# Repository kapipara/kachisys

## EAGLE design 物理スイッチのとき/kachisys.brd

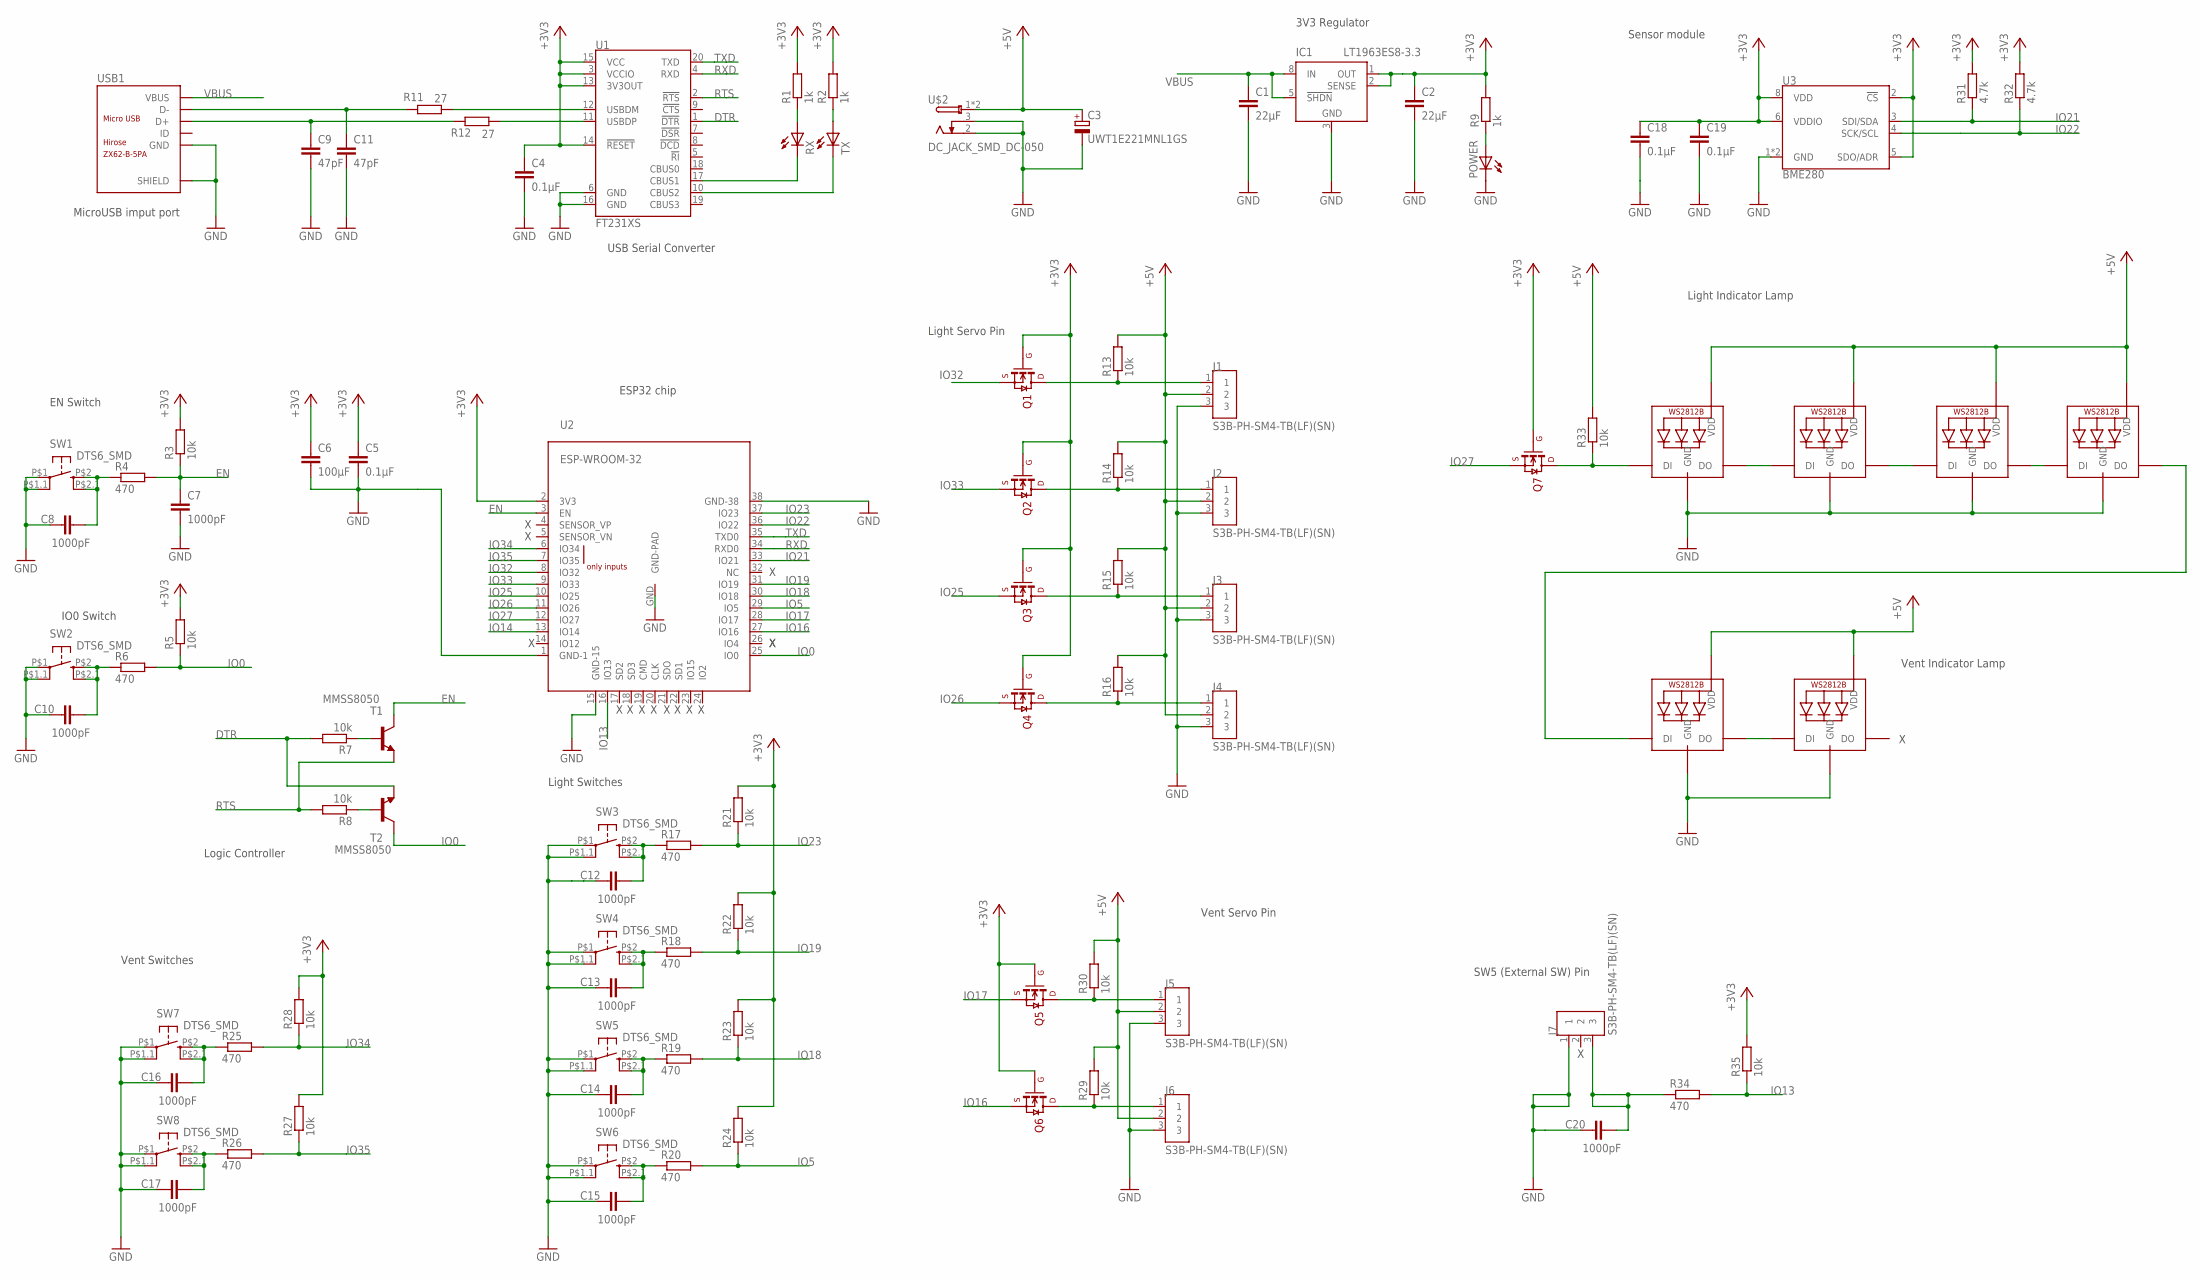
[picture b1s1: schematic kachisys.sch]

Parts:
C1, C2: 22μF; C2012
C3: UWT1E221MNL1GS; NICHICON-ALMINUM-CAPACITOR-8MM
C4, C5, C18, C19: 0.1μF; C0603
C6: 100μF; C3225
C7, C8, C10, C12, C13, C14, C15, C16, C17, C20: 1000pF; C0603
C9, C11: 47pF; C1608
IC1: LT1963ES8-3.3; SOIC8
J1, J2, J3, J4, J5, J6, J7: S3B-PH-SM4-TB(LF)(SN); JST_S3B-PH-SM4-TB(LF)(SN)
LED1, LED2, LED3, LED4, LED5, LED6: WS2812B_5050N; WS2812B-NARROW
POWER: LEDCHIP-LED0603; CHIP-LED0603
Q1, Q2, Q3, Q4, Q5, Q6, Q7: BSS138; SOT-23
R1, R2, R9: 1k; R0603
R3, R5, R7, R8, R13, R14, R15, R16, R21, R22, R23, R24, R27, R28, R29, R30, R33, R35: 10k; R0603
R4, R6, R17, R18, R19, R20, R25, R26, R34: 470; R0603
R11, R12: 27; R0603
R31, R32: 4.7k; R0603
RX: LEDCHIP-LED0603; CHIP-LED0603
SW1, SW2, SW3, SW4, SW5, SW6, SW7, SW8: DTS6_SMD; SKRPACE010
T1, T2: MMSS8050; SOT23-EBC
TX: LEDCHIP-LED0603; CHIP-LED0603
U1: FT231XS; SSOP20_L
U2: ESP-WROOM-32
U3: BME280; LGA-8-2.5X2.5
U$2: DC_JACK_SMD_DC-050
USB1: ZX62-B-5PA; MICRO-USB5+6P-SMD-0.65-AB

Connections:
+3V3: C2.1, C4.1, C5.1, C6.1, C18.1, C19.1, IC1.1 (OUT), IC1.2 (SENSE), Q1.G, Q2.G, Q3.G, Q4.G, Q5.G, Q6.G, Q7.G, R1.2, R2.2, R3.2, R5.2, R9.2, R21.2, R22.2, R23.2, R24.2, R27.2, R28.2, R31.2, R32.2, R35.2, U1.3 (VCCIO), U1.13 (3V3OUT), U1.14 (!RESET), U1.15 (VCC), U2.2 (3V3), U3.2 (!CS), U3.5 (SDO/ADR), U3.6 (VDDIO), U3.8 (VDD)
+5V: C3.POS (+), J1.2, J2.2, J3.2, J4.2, J5.2, J6.2, LED1.1-VDD (VDD), LED2.1-VDD (VDD), LED3.1-VDD (VDD), LED4.1-VDD (VDD), LED5.1-VDD (VDD), LED6.1-VDD (VDD), R13.2, R14.2, R15.2, R16.2, R29.2, R30.2, R33.2, U$2.1, U$2.1-1 (1)
DTR: R7.2, T2.E, U1.1 (!DTR)
EN: C7.1, R3.1, R4.2, T1.C, U2.3 (EN)
GND: C1.2, C2.2, C3.NEG (-), C4.2, C5.2, C6.2, C7.2, C8.1, C9.2, C10.1, C11.2, C12.1, C13.1, C14.1, C15.1, C16.1, C17.1, C18.2, C19.2, C20.1, IC1.3 (GND), IC1.6 (GND), IC1.7 (GND), J1.3, J2.3, J3.3, J4.3, J5.3, J6.3, J7.1, LED1.3-GND (GND), LED2.3-GND (GND), LED3.3-GND (GND), LED4.3-GND (GND), LED5.3-GND (GND), LED6.3-GND (GND), POWER.C, SW1.P$1, SW1.P$1.1 (P1), SW2.P$1, SW2.P$1.1 (P1), SW3.P$1, SW3.P$1.1 (P1), SW4.P$1, SW4.P$1.1 (P1), SW5.P$1, SW5.P$1.1 (P1), SW6.P$1, SW6.P$1.1 (P1), SW7.P$1, SW7.P$1.1 (P1), SW8.P$1, SW8.P$1.1 (P1), U1.6 (GND), U1.16 (GND), U2.1 (GND-1), U2.15 (GND-15), U2.38 (GND-38), U2.GND (GND-PAD), U3.1 (GND), U3.7 (GND), U$2.2, U$2.3, USB1.5 (GND), USB1.P1 (SHIELD), USB1.P2 (SHIELD), USB1.P3 (SHIELD), USB1.P4 (SHIELD), USB1.P5 (SHIELD), USB1.P6 (SHIELD)
IO0: R5.1, R6.2, T2.C, U2.25 (IO0)
IO5: R20.2, R24.1, U2.29 (IO5)
IO13: R34.2, R35.1, U2.16 (IO13)
IO14: U2.13 (IO14)
IO16: Q6.S, U2.27 (IO16)
IO17: Q5.S, U2.28 (IO17)
IO18: R19.2, R23.1, U2.30 (IO18)
IO19: R18.2, R22.1, U2.31 (IO19)
IO21: R31.1, U2.33 (IO21), U3.3 (SDI/SDA)
IO22: R32.1, U2.36 (IO22), U3.4 (SCK/SCL)
IO23: R17.2, R21.1, U2.37 (IO23)
IO25: Q3.S, U2.10 (IO25)
IO26: Q4.S, U2.11 (IO26)
IO27: Q7.S, U2.12 (IO27)
IO32: Q1.S, U2.8 (IO32)
IO33: Q2.S, U2.9 (IO33)
IO34: R25.2, R28.1, U2.6 (IO34)
IO35: R26.2, R27.1, U2.7 (IO35)
unnamed: C11.1, R11.2, USB1.2 (D-)
unnamed: C9.1, R12.2, USB1.3 (D+)
unnamed: RX.C, U1.17 (CBUS1)
unnamed: TX.C, U1.10 (CBUS2)
unnamed: C8.2, R4.1, SW1.P$2 (S), SW1.P$2.1 (S1)
unnamed: R1.1, RX.A
unnamed: R2.1, TX.A
unnamed: R7.1, T1.B
unnamed: R8.1, T2.B
unnamed: POWER.A, R9.1
unnamed: C10.2, R6.1, SW2.P$2 (S), SW2.P$2.1 (S1)
unnamed: R11.1, U1.12 (USBDM)
unnamed: R12.1, U1.11 (USBDP)
unnamed: J1.1, Q1.D, R13.1
unnamed: J2.1, Q2.D, R14.1
unnamed: J3.1, Q3.D, R15.1
unnamed: J4.1, Q4.D, R16.1
unnamed: C12.2, R17.1, SW3.P$2 (S), SW3.P$2.1 (S1)
unnamed: LED1.2-DOUT (DO), LED2.4-DIN (DI)
unnamed: C13.2, R18.1, SW4.P$2 (S), SW4.P$2.1 (S1)
unnamed: C14.2, R19.1, SW5.P$2 (S), SW5.P$2.1 (S1)
unnamed: C15.2, R20.1, SW6.P$2 (S), SW6.P$2.1 (S1)
unnamed: LED2.2-DOUT (DO), LED3.4-DIN (DI)
unnamed: C16.2, R25.1, SW7.P$2 (S), SW7.P$2.1 (S1)
unnamed: C17.2, R26.1, SW8.P$2 (S), SW8.P$2.1 (S1)
unnamed: LED3.2-DOUT (DO), LED4.4-DIN (DI)
unnamed: LED4.2-DOUT (DO), LED5.4-DIN (DI)
unnamed: J5.1, Q5.D, R30.1
unnamed: J6.1, Q6.D, R29.1
unnamed: LED5.2-DOUT (DO), LED6.4-DIN (DI)
unnamed: LED1.4-DIN (DI), Q7.D, R33.1
unnamed: C20.2, J7.3, R34.1
RTS: R8.2, T1.E, U1.2 (!RTS)
RXD: U1.4 (RXD), U2.34 (RXD0)
TXD: U1.20 (TXD), U2.35 (TXD0)
VBUS: C1.1, IC1.5 (!SHDN), IC1.8 (IN), USB1.1 (VBUS)

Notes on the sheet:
3V3 Regulator
USB Serial Converter
MicroUSB imput port
EN Switch
IO0 Switch
Logic Controller
ESP32 chip
Light Servo Pin
Light Switches
Vent Switches
Sensor module
Vent Servo Pin
Light Indicator Lamp
Vent Indicator Lamp
SW5 (External SW) Pin

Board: 2 copper layers, 93 parts (0 on the bottom side), 58 nets, no tracks yet.

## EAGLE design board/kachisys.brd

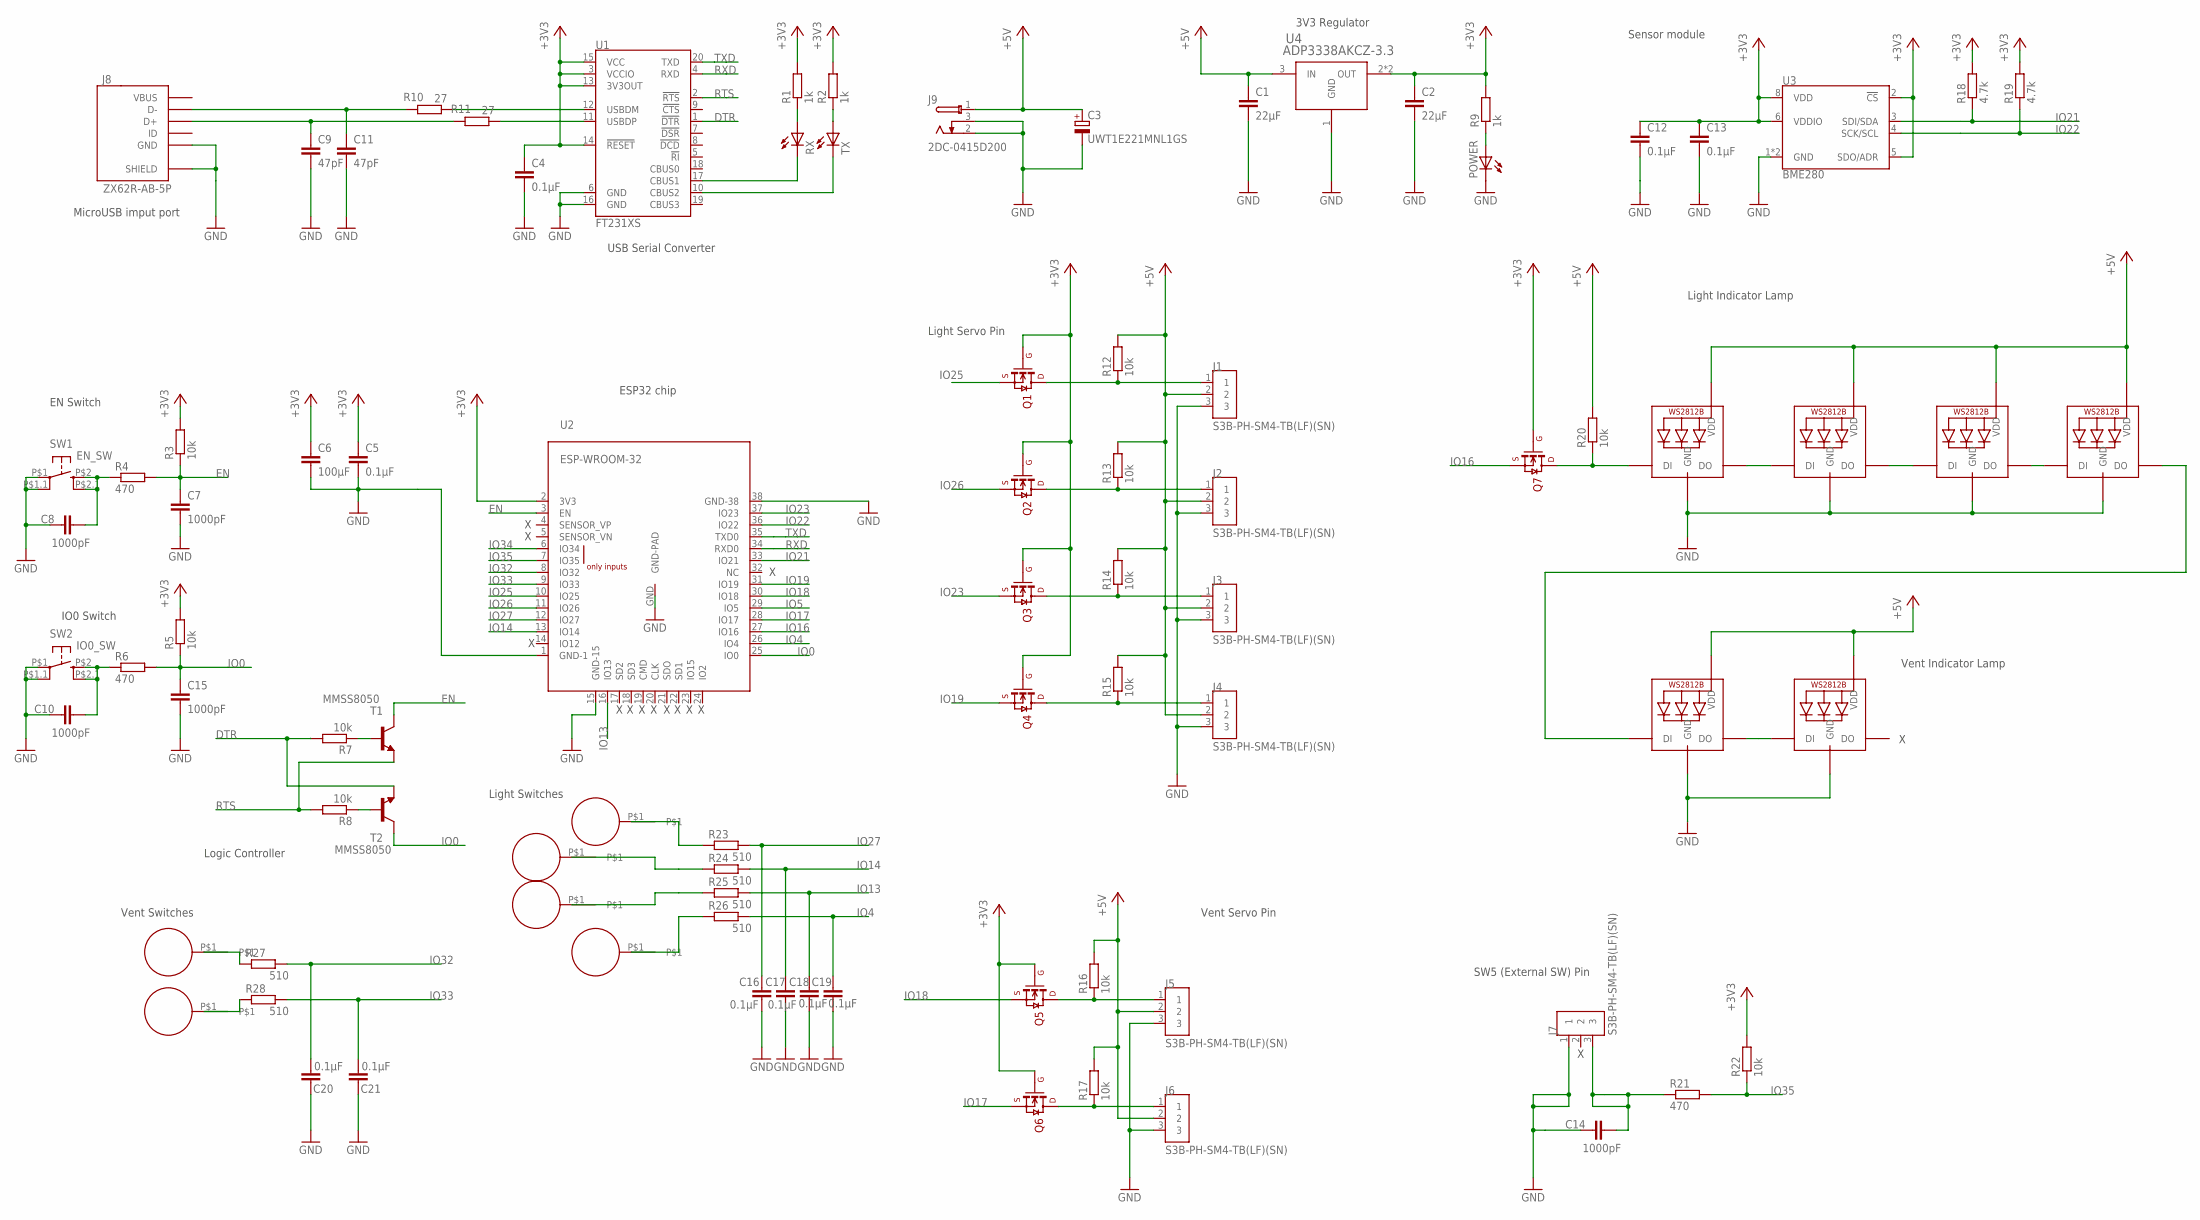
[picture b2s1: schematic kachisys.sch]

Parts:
C1, C2: 22μF; C2012
C3: UWT1E221MNL1GS; NICHICON-ALMINUM-CAPACITOR-8MM
C4, C5, C12, C13, C16, C17, C18, C19, C20, C21: 0.1μF; C0603
C6: 100μF; C3225
C7, C8, C10, C14, C15: 1000pF; C0603
C9, C11: 47pF; C1608
J1, J2, J3, J4, J5, J6, J7: S3B-PH-SM4-TB(LF)(SN); JST_S3B-PH-SM4-TB(LF)(SN)
J8: ZX62R-AB-5P; ZX62R-B-5PA
J9: 2DC-0415D200
LED1, LED2, LED3, LED4, LED5, LED6: WS2812B_5050N; WS2812B-NARROW
POWER: LEDCHIP-LED0603; CHIP-LED0603
Q1, Q2, Q3, Q4, Q5, Q6, Q7: BSS138; SOT-23
R1, R2, R9: 1k; R0603
R3, R5, R7, R8, R12, R13, R14, R15, R16, R17, R20, R22: 10k; R0603
R4, R6, R21: 470; R0603
R10, R11: 27; R0603
R18, R19: 4.7k; R0603
R23, R24, R25, R26, R27, R28: 510; R0603
RX: LEDCHIP-LED0603; CHIP-LED0603
SW1: EN_SW; SKRPACE010
SW2: IO0_SW; SKRPACE010
T1, T2: MMSS8050; SOT23-EBC
TPAD1, TPAD2, TPAD3, TPAD4, TPAD5, TPAD6: ESP32-TOUCHPAD; ESP32-TOUCHPAD-10MM
TX: LEDCHIP-LED0603; CHIP-LED0603
U1: FT231XS; SSOP20_L
U2: ESP-WROOM-32
U3: BME280; LGA-8-2.5X2.5
U4: ADP3338AKCZ-3.3; SOT233

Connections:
+3V3: C2.1, C4.1, C5.1, C6.1, C12.1, C13.1, Q1.G, Q2.G, Q3.G, Q4.G, Q5.G, Q6.G, Q7.G, R1.2, R2.2, R3.2, R5.2, R9.2, R18.2, R19.2, R22.2, U1.3 (VCCIO), U1.13 (3V3OUT), U1.14 (!RESET), U1.15 (VCC), U2.2 (3V3), U3.2 (!CS), U3.5 (SDO/ADR), U3.6 (VDDIO), U3.8 (VDD), U4.2 (OUT), U4.4 (OUT)
+5V: C1.1, C3.POS (+), J1.2, J2.2, J3.2, J4.2, J5.2, J6.2, J9.1, LED1.1-VDD (VDD), LED2.1-VDD (VDD), LED3.1-VDD (VDD), LED4.1-VDD (VDD), LED5.1-VDD (VDD), LED6.1-VDD (VDD), R12.2, R13.2, R14.2, R15.2, R16.2, R17.2, R20.2, U4.3 (IN)
DTR: R7.2, T2.E, U1.1 (!DTR)
EN: C7.1, R3.1, R4.2, T1.C, U2.3 (EN)
GND: C1.2, C2.2, C3.NEG (-), C4.2, C5.2, C6.2, C7.2, C8.1, C9.2, C10.1, C11.2, C12.2, C13.2, C14.1, C15.2, C16.2, C17.2, C18.2, C19.2, C20.1, C21.1, J1.3, J2.3, J3.3, J4.3, J5.3, J6.3, J7.1, J8.GND, J8.SHIELD@1 (SHIELD), J8.SHIELD@2 (SHIELD), J8.SHIELD@3 (SHIELD), J8.SHIELD@4 (SHIELD), J9.2, J9.3, LED1.3-GND (GND), LED2.3-GND (GND), LED3.3-GND (GND), LED4.3-GND (GND), LED5.3-GND (GND), LED6.3-GND (GND), POWER.C, SW1.P$1, SW1.P$1.1 (P1), SW2.P$1, SW2.P$1.1 (P1), U1.6 (GND), U1.16 (GND), U2.1 (GND-1), U2.15 (GND-15), U2.38 (GND-38), U2.GND (GND-PAD), U3.1 (GND), U3.7 (GND), U4.1 (GND)
IO0: C15.1, R5.1, R6.2, T2.C, U2.25 (IO0)
IO4: C19.1, R26.2, U2.26 (IO4)
IO5: U2.29 (IO5)
IO13: C18.1, R25.2, U2.16 (IO13)
IO14: C17.1, R24.2, U2.13 (IO14)
IO16: Q7.S, U2.27 (IO16)
IO17: Q6.S, U2.28 (IO17)
IO18: Q5.S, U2.30 (IO18)
IO19: Q4.S, U2.31 (IO19)
IO21: R18.1, U2.33 (IO21), U3.3 (SDI/SDA)
IO22: R19.1, U2.36 (IO22), U3.4 (SCK/SCL)
IO23: Q3.S, U2.37 (IO23)
IO25: Q1.S, U2.10 (IO25)
IO26: Q2.S, U2.11 (IO26)
IO27: C16.1, R23.2, U2.12 (IO27)
IO32: C20.2, R27.2, U2.8 (IO32)
IO33: C21.2, R28.2, U2.9 (IO33)
IO34: U2.6 (IO34)
IO35: R21.2, R22.1, U2.7 (IO35)
unnamed: R27.1, TPAD5.P$1
unnamed: C11.1, J8.D-, R10.2
unnamed: C9.1, J8.D+, R11.2
unnamed: RX.C, U1.17 (CBUS1)
unnamed: TX.C, U1.10 (CBUS2)
unnamed: C8.2, R4.1, SW1.P$2 (S), SW1.P$2.1 (S1)
unnamed: R1.1, RX.A
unnamed: R2.1, TX.A
unnamed: R7.1, T1.B
unnamed: R8.1, T2.B
unnamed: POWER.A, R9.1
unnamed: C10.2, R6.1, SW2.P$2 (S), SW2.P$2.1 (S1)
unnamed: R28.1, TPAD6.P$1
unnamed: R10.1, U1.12 (USBDM)
unnamed: R11.1, U1.11 (USBDP)
unnamed: J1.1, Q1.D, R12.1
unnamed: J2.1, Q2.D, R13.1
unnamed: J3.1, Q3.D, R14.1
unnamed: J4.1, Q4.D, R15.1
unnamed: LED1.2-DOUT (DO), LED2.4-DIN (DI)
unnamed: LED2.2-DOUT (DO), LED3.4-DIN (DI)
unnamed: LED3.2-DOUT (DO), LED4.4-DIN (DI)
unnamed: LED4.2-DOUT (DO), LED5.4-DIN (DI)
unnamed: J5.1, Q5.D, R16.1
unnamed: J6.1, Q6.D, R17.1
unnamed: LED5.2-DOUT (DO), LED6.4-DIN (DI)
unnamed: LED1.4-DIN (DI), Q7.D, R20.1
unnamed: C14.2, J7.3, R21.1
unnamed: R23.1, TPAD1.P$1
unnamed: R24.1, TPAD2.P$1
unnamed: R25.1, TPAD3.P$1
unnamed: R26.1, TPAD4.P$1
RTS: R8.2, T1.E, U1.2 (!RTS)
RXD: U1.4 (RXD), U2.34 (RXD0)
TXD: U1.20 (TXD), U2.35 (TXD0)

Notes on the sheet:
3V3 Regulator
USB Serial Converter
MicroUSB imput port
EN Switch
IO0 Switch
Logic Controller
ESP32 chip
Light Servo Pin
Light Switches
Vent Switches
Sensor module
Vent Servo Pin
Light Indicator Lamp
Vent Indicator Lamp
SW5 (External SW) Pin

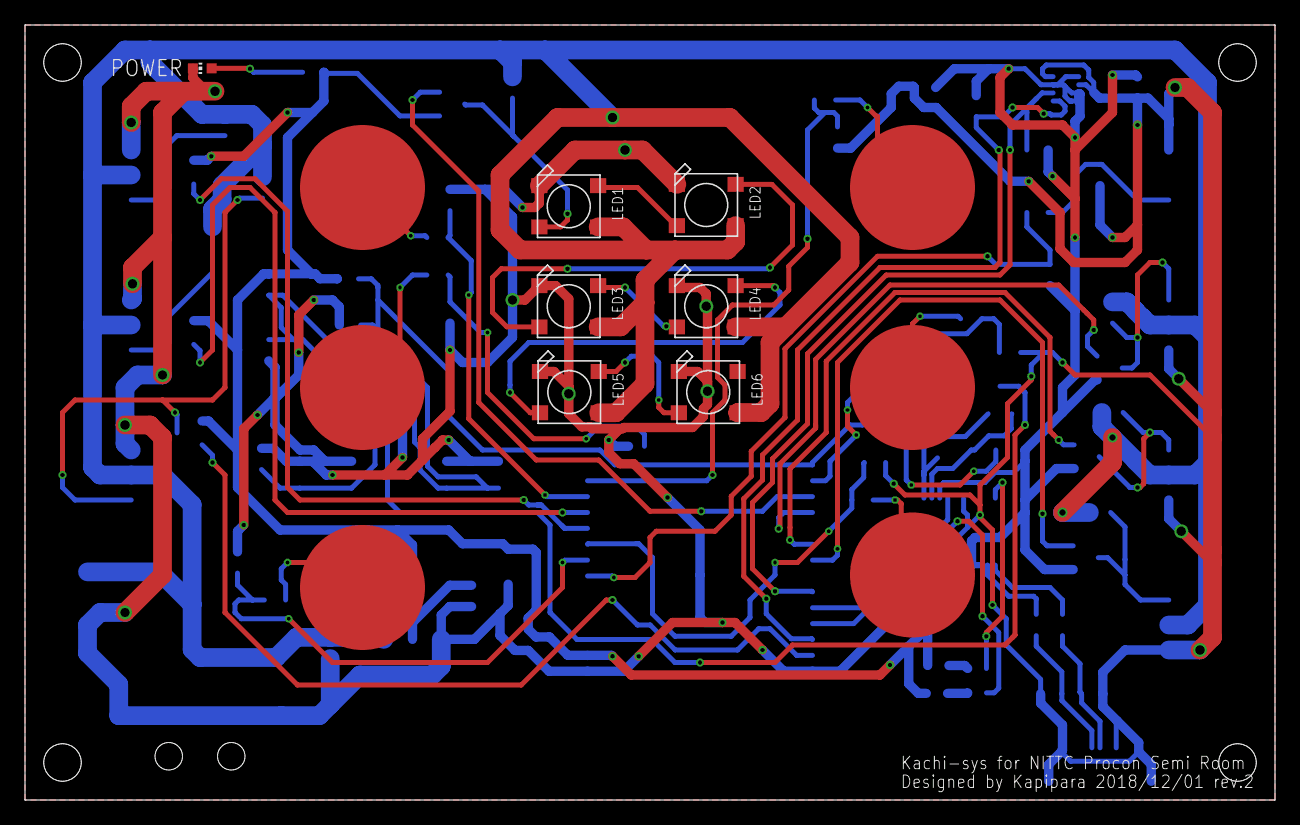
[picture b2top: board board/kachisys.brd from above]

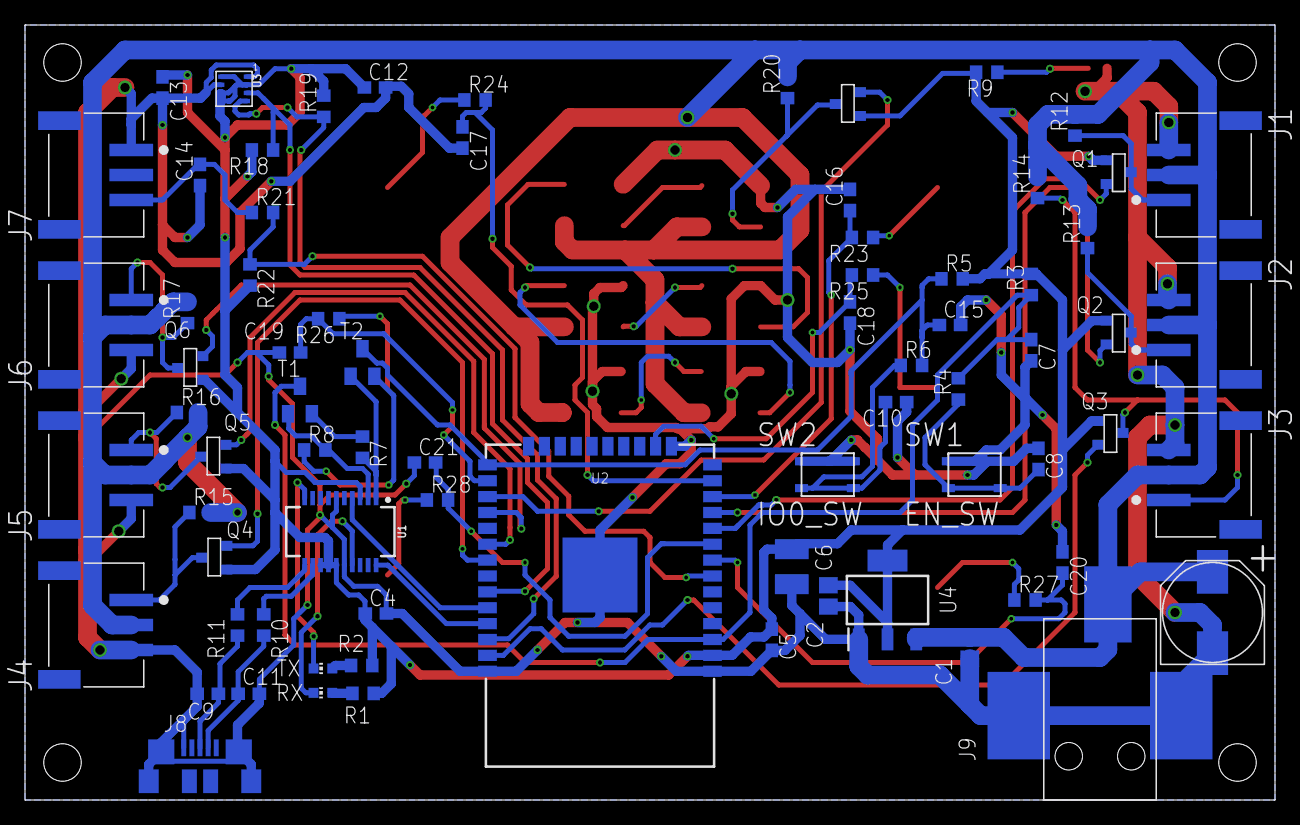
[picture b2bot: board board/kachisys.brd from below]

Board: 2 copper layers, 100.0 x 62.0 mm, 88 parts (75 on the bottom side), 57 nets.

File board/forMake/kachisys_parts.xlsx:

Part | Value | Device | Description
C1 | 22μF | C-EUC2012 | Capacitor
C2 | 22μF | C-EUC2012 | Capacitor
C3 | UWT1E221MNL1GS | ﾆﾁｺﾝ 電解ｺﾝ 8mmデンカ | Capacitor
C4 | 0.1μF | C-EUC0603 | Capacitor
C5 | 0.1μF | C-EUC0603 | Capacitor
C6 | 100μF | C-EUC3225 | Capacitor
C7 | 1000pF | C-EUC0603 | Capacitor
C8 | 1000pF | C-EUC0603 | Capacitor
C9 | 47pF | C-EUC1608 | Capacitor
C10 | 1000pF | C-EUC0603 | Capacitor
C11 | 47pF | C-EUC1608 | Capacitor
C12 | 0.1μF | C-EUC0603 | Capacitor
C13 | 0.1μF | C-EUC0603 | Capacitor
C14 | 1000pF | C-EUC0603 | Capacitor
C15 | 1000pF | C-EUC0603 | Capacitor
C16 | 0.1μF | C-EUC0603 | Capacitor
C17 | 0.1μF | C-EUC0603 | Capacitor
C18 | 0.1μF | C-EUC0603 | Capacitor
C19 | 0.1μF | C-EUC0603 | Capacitor
C20 | 0.1μF | C-EUC0603 | Capacitor
C21 | 0.1μF | C-EUC0603 | Capacitor
IC1 | LT1963ES8-3.3 | LT1963ES8-3.3 | 3V3 Regulator
J1 | S3B-PH-SM4-TB(LF)(SN) | S3B-PH-SM4-TB(LF)(SN) | PHコネクタ 3端子タンシ
J2 | S3B-PH-SM4-TB(LF)(SN) | S3B-PH-SM4-TB(LF)(SN) | PHコネクタ 3端子タンシ
J3 | S3B-PH-SM4-TB(LF)(SN) | S3B-PH-SM4-TB(LF)(SN) | PHコネクタ 3端子タンシ
J4 | S3B-PH-SM4-TB(LF)(SN) | S3B-PH-SM4-TB(LF)(SN) | PHコネクタ 3端子タンシ
J5 | S3B-PH-SM4-TB(LF)(SN) | S3B-PH-SM4-TB(LF)(SN) | PHコネクタ 3端子タンシ
J6 | S3B-PH-SM4-TB(LF)(SN) | S3B-PH-SM4-TB(LF)(SN) | PHコネクタ 3端子タンシ
J7 | S3B-PH-SM4-TB(LF)(SN) | S3B-PH-SM4-TB(LF)(SN) | PHコネクタ 3端子タンシ
J8 | ZX62R-AB-5P | ZX62R-AB-5P | Micro USB
J9 | 2DC-0415D200 | 2DC-0415D200 | DC Jack
LED1 | WS2812B_5050N | WS2812B_5050N | RGB LED
LED2 | WS2812B_5050N | WS2812B_5050N | RGB LED
LED3 | WS2812B_5050N | WS2812B_5050N | RGB LED
LED4 | WS2812B_5050N | WS2812B_5050N | RGB LED
LED5 | WS2812B_5050N | WS2812B_5050N | RGB LED
LED6 | WS2812B_5050N | WS2812B_5050N | RGB LED
POWER | LED | LEDCHIP-LED0603 | chip LED
Q1 | BSS138 | BSS138 | レベルシフト用FETヨウ
Q2 | BSS138 | BSS138 | レベルシフト用FETヨウ
Q3 | BSS138 | BSS138 | レベルシフト用FETヨウ
Q4 | BSS138 | BSS138 | レベルシフト用FETヨウ
Q5 | BSS138 | BSS138 | レベルシフト用FETヨウ
Q6 | BSS138 | BSS138 | レベルシフト用FETヨウ
Q7 | BSS138 | BSS138 | レベルシフト用FETヨウ
R1 | 1k | R-EU_R0603 | Resistor
R2 | 1k | R-EU_R0603 | Resistor
R3 | 10k | R-EU_R0603 | Resistor
R4 | 470 | R-EU_R0603 | Resistor
R5 | 10k | R-EU_R0603 | Resistor
R6 | 470 | R-EU_R0603 | Resistor
R7 | 10k | R-EU_R0603 | Resistor
R8 | 10k | R-EU_R0603 | Resistor
R9 | 1k | R-EU_R0603 | Resistor
R10 | 27 | R-EU_R0603 | Resistor
R11 | 27 | R-EU_R0603 | Resistor
R12 | 10k | R-EU_R0603 | Resistor
R13 | 10k | R-EU_R0603 | Resistor
R14 | 10k | R-EU_R0603 | Resistor
R15 | 10k | R-EU_R0603 | Resistor
R16 | 10k | R-EU_R0603 | Resistor
R17 | 10k | R-EU_R0603 | Resistor
R18 | 4.7k | R-EU_R0603 | Resistor
R19 | 4.7k | R-EU_R0603 | Resistor
R20 | 10k | R-EU_R0603 | Resistor
R21 | 470 | R-EU_R0603 | Resistor
R22 | 10k | R-EU_R0603 | Resistor
R23 | 510 | R-EU_R0603 | Resistor
R24 | 510 | R-EU_R0603 | Resistor
R25 | 510 | R-EU_R0603 | Resistor
R26 | 510 | R-EU_R0603 | Resistor
R27 | 510 | R-EU_R0603 | Resistor
R28 | 510 | R-EU_R0603 | Resistor
SW1 | EN_SW | DTS6_SMD | ESP32用スイッチヨウ
SW2 | IO0_SW | DTS6_SMD | ESP32用スイッチヨウ
T1 | MMSS8050 | NPN-SOT23-EBC | NPN Transistror
T2 | MMSS8050 | NPN-SOT23-EBC | NPN Transistror
TPAD1 | ESP32-TOUCHPAD | ESP32-TOUCHPAD | 表面タッチパッドオモテメン
TPAD2 | ESP32-TOUCHPAD | ESP32-TOUCHPAD | 表面タッチパッドオモテメン
TPAD3 | ESP32-TOUCHPAD | ESP32-TOUCHPAD | 表面タッチパッドオモテメン
TPAD4 | ESP32-TOUCHPAD | ESP32-TOUCHPAD | 表面タッチパッドオモテメン
TPAD5 | ESP32-TOUCHPAD | ESP32-TOUCHPAD | 表面タッチパッドオモテメン
TPAD6 | ESP32-TOUCHPAD | ESP32-TOUCHPAD | 表面タッチパッドオモテメン
TX | LED | LEDCHIP-LED0603 | chip LED
RX | LED | LEDCHIP-LED0603 | chip LED
U1 | FT231XS | FT231XS | USB⇔UART変換チップヘンカン
U2 | ESP-WROOM-32 | ESP-WROOM-32 | ESP32
U3 | BME280 | BME280 | 温湿度センサオンシツド

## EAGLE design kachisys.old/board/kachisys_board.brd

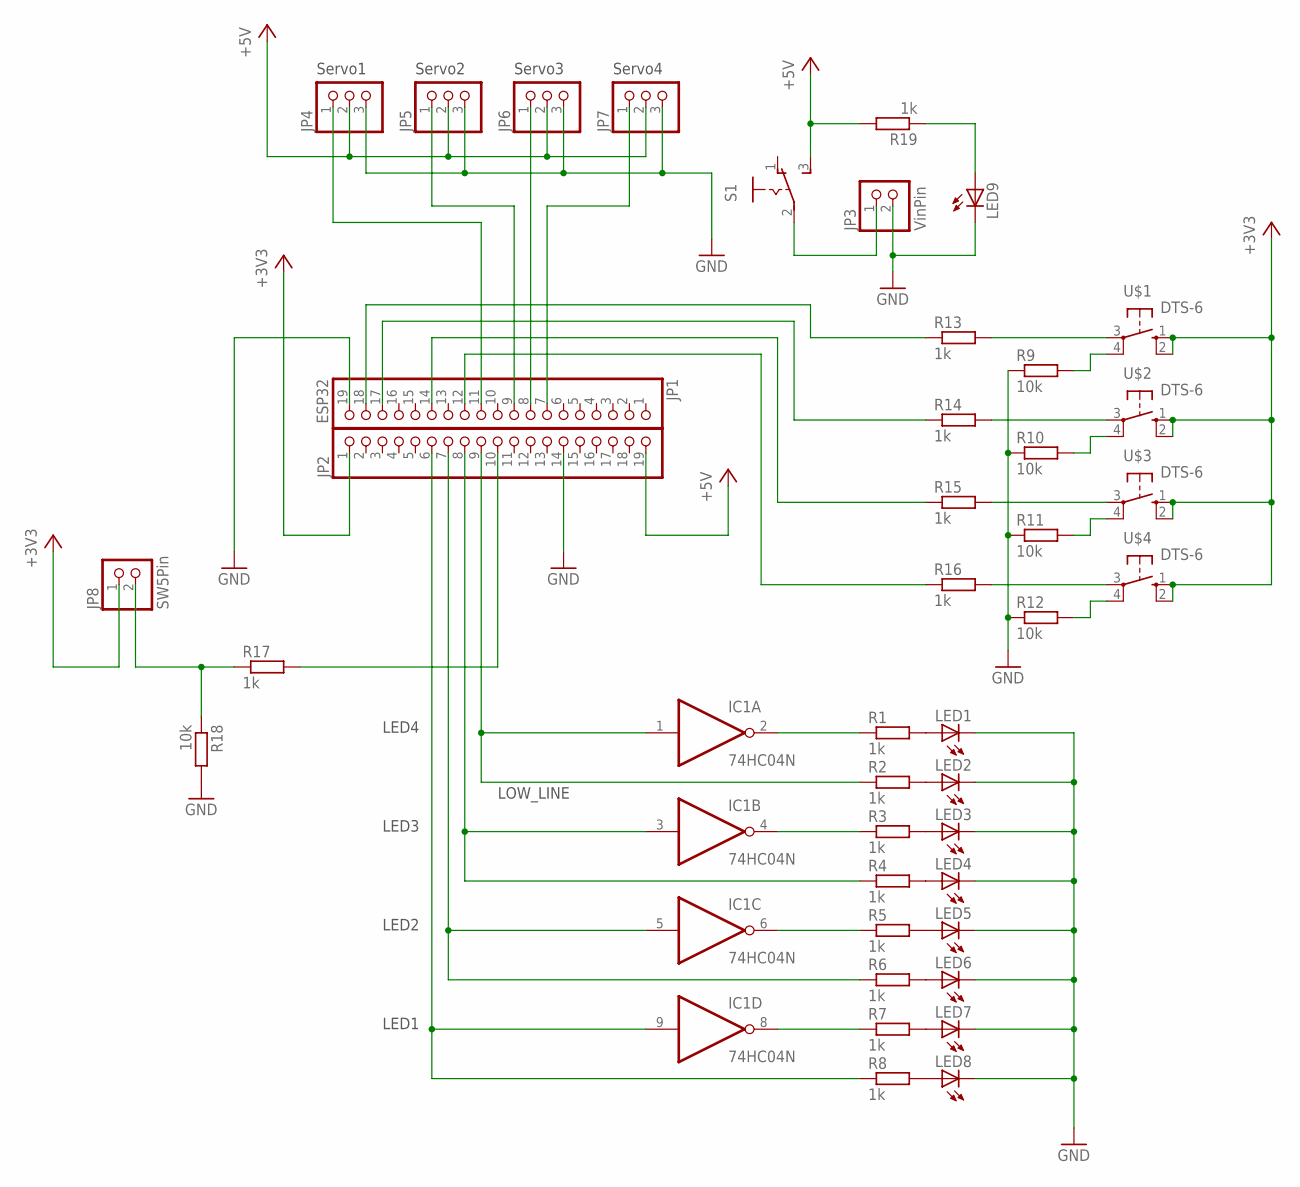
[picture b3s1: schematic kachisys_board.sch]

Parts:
IC1: 74HC04N; DIL14
JP1: ESP32; 1X19
JP2: 1X19
JP3: VinPin; 1X02/90
JP4, JP5, JP6, JP7: PINHD-1X3; 1X03
JP8: SW5Pin; 1X02/90
LED1, LED2, LED3, LED4, LED5, LED6, LED7, LED8, LED9: LED3MM
R1, R2, R3, R4, R5, R6, R7, R8, R13, R14, R15, R16, R17, R19: 1k; M2012
R9, R10, R11, R12, R18: 10k; M2012
S1: 255SB
U$1, U$2, U$3, U$4: DTS-6; DTS6

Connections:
+3V3: JP2.1, JP8.1, U$1.1 (S), U$1.2 (S1), U$2.1 (S), U$2.2 (S1), U$3.1 (S), U$3.2 (S1), U$4.1 (S), U$4.2 (S1)
+5V: JP2.19, JP4.2, JP5.2, JP6.2, JP7.2, R19.2, S1.3 (S)
GND: IC1.7 (GND), JP1.19, JP2.14, JP3.2, JP4.3, JP5.3, JP6.3, JP7.3, LED1.K (C), LED2.K (C), LED3.K (C), LED4.K (C), LED5.K (C), LED6.K (C), LED7.K (C), LED8.K (C), LED9.K (C), R9.1, R10.1, R11.1, R12.1, R18.2
unnamed: IC1.9 (I), JP2.6, R8.1
unnamed: IC1.5 (I), JP2.7, R6.1
unnamed: IC1.3 (I), JP2.8, R4.1
unnamed: IC1.1 (I), JP2.9, R2.1
unnamed: IC1.2 (O), R1.1
unnamed: IC1.4 (O), R3.1
unnamed: IC1.6 (O), R5.1
unnamed: IC1.8 (O), R7.1
unnamed: LED1.A, R1.2
unnamed: LED2.A, R2.2
unnamed: LED3.A, R3.2
unnamed: LED4.A, R4.2
unnamed: LED5.A, R5.2
unnamed: LED6.A, R6.2
unnamed: LED7.A, R7.2
unnamed: LED8.A, R8.2
unnamed: R9.2, U$1.4 (P1)
unnamed: R10.2, U$2.4 (P1)
unnamed: R11.2, U$3.4 (P1)
unnamed: R12.2, U$4.4 (P1)
unnamed: JP8.2, R17.1, R18.1
unnamed: R13.2, U$1.3
unnamed: R14.2, U$2.3
unnamed: R15.2, U$3.3
unnamed: JP1.7, JP7.1
unnamed: JP1.8, JP6.1
unnamed: JP1.9, JP5.1
unnamed: JP1.11, JP4.1
unnamed: R16.2, U$4.3
unnamed: JP1.12, R16.1
unnamed: JP1.14, R15.1
unnamed: JP1.17, R14.1
unnamed: JP1.18, R13.1
unnamed: JP3.1, S1.2
unnamed: LED9.A, R19.1
unnamed: JP2.10, R17.2
VCC: IC1.14 (VCC)

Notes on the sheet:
LOW_LINE
LED1
LED2
LED3
LED4
Servo1
Servo2
Servo3
Servo4

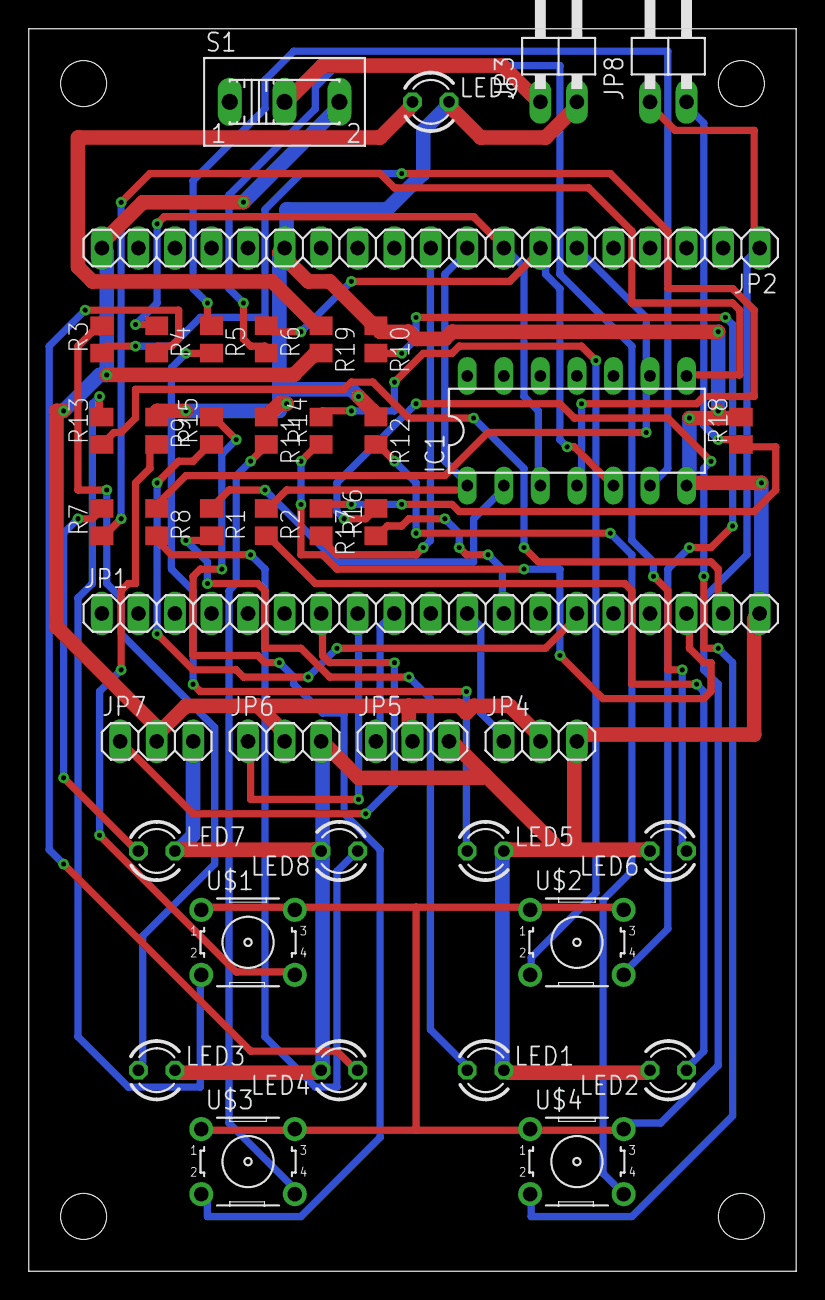
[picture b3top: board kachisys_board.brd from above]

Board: 2 copper layers, 53.3 x 86.4 mm, 42 parts (0 on the bottom side), 39 nets.

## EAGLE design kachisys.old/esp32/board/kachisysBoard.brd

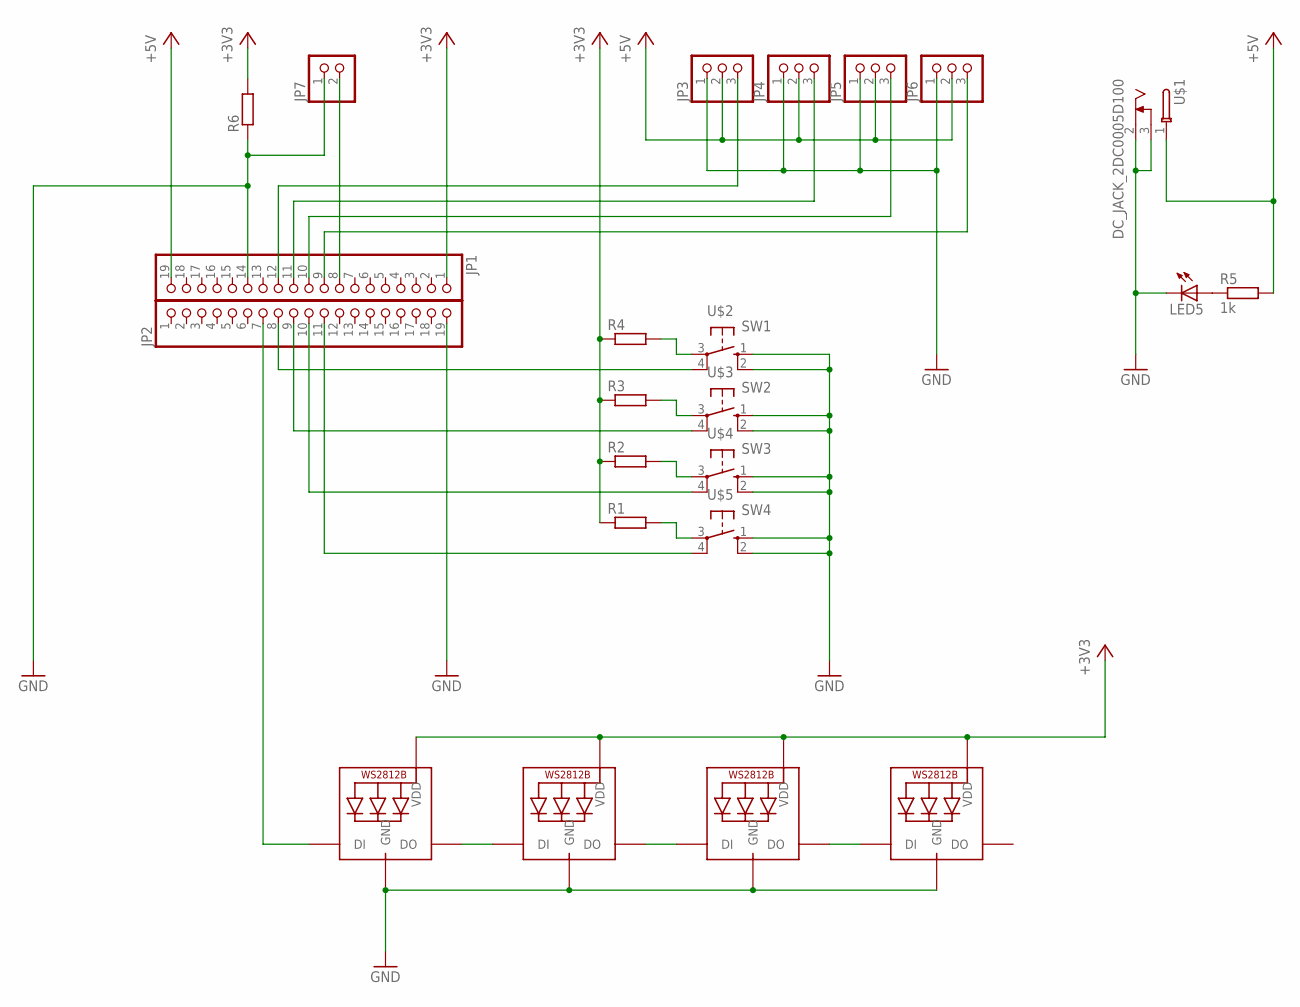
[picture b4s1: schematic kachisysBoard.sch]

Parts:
JP1, JP2: PINHD-1X19; 1X19
JP3, JP4, JP5, JP6: PINHD-1X3/90; 1X03/90
JP7: PINHD-1X2/90; 1X02/90
LED1, LED2, LED3, LED4: WS2812B5050; WS2812B
LED5: LED3MM
R1, R2, R3, R4, R6: R-EU_M3216; M3216
R5: 1k; M3216
U$1: DC_JACK_2DC0005D100
U$2: SW1; DTS6
U$3: SW2; DTS6
U$4: SW3; DTS6
U$5: SW4; DTS6

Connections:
+3V3: JP1.1, LED1.1-VDD (VDD), LED2.1-VDD (VDD), LED3.1-VDD (VDD), LED4.1-VDD (VDD), R1.1, R2.1, R3.1, R4.1, R6.2
+5V: JP1.19, JP3.2, JP4.2, JP5.2, JP6.2, R5.2, U$1.1
GND: JP1.14, JP2.19, JP3.1, JP4.1, JP5.1, JP6.1, JP7.1, LED1.3-GND (GND), LED2.3-GND (GND), LED3.3-GND (GND), LED4.3-GND (GND), LED5.K (C), R6.1, U$1.2, U$1.3, U$2.1 (S), U$2.2 (S1), U$3.1 (S), U$3.2 (S1), U$4.1 (S), U$4.2 (S1), U$5.1 (S), U$5.2 (S1)
unnamed: R1.2, U$5.3
unnamed: LED1.2-DOUT (DO), LED2.4-DIN (DI)
unnamed: LED2.2-DOUT (DO), LED3.4-DIN (DI)
unnamed: LED3.2-DOUT (DO), LED4.4-DIN (DI)
unnamed: R2.2, U$4.3
unnamed: R3.2, U$3.3
unnamed: R4.2, U$2.3
unnamed: JP2.7, LED1.4-DIN (DI)
unnamed: JP2.8, U$2.4 (P1)
unnamed: JP2.9, U$3.4 (P1)
unnamed: JP2.10, U$4.4 (P1)
unnamed: JP2.11, U$5.4 (P1)
unnamed: LED5.A, R5.1
unnamed: JP1.11, JP4.3
unnamed: JP1.10, JP5.3
unnamed: JP1.9, JP6.3
unnamed: JP1.8, JP7.2

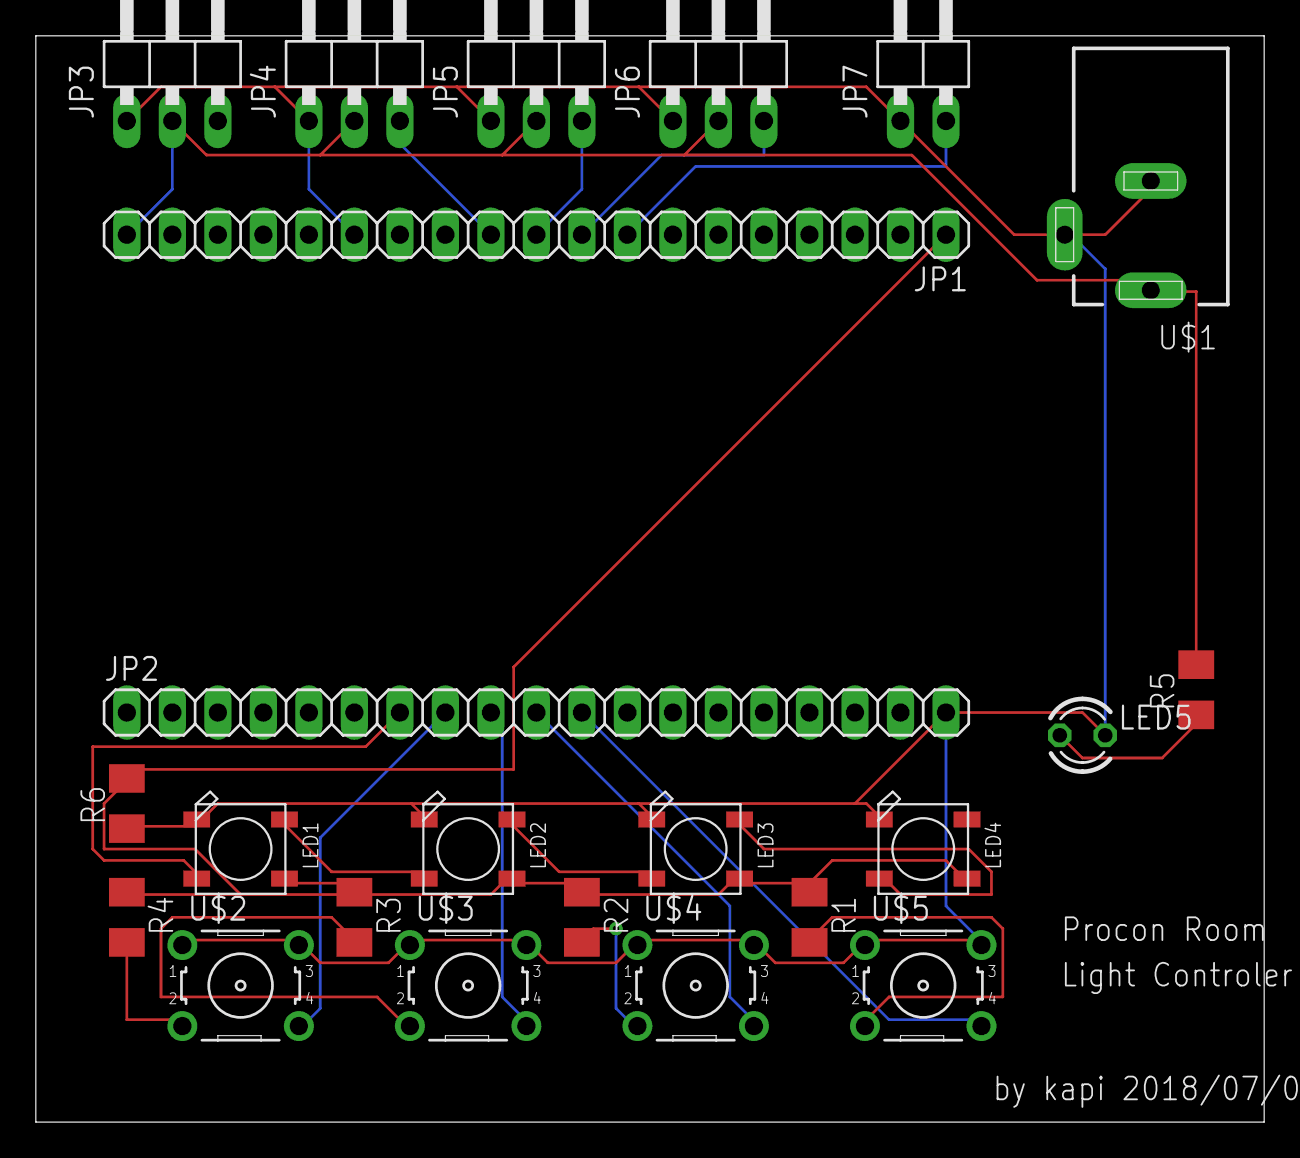
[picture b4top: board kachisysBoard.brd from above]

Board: 2 copper layers, 68.6 x 60.6 mm, 23 parts (0 on the bottom side), 20 nets.

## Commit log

2018-10-02 board data upload
2018-10-15 旧kachisysの遺産ファイルをアップロード
2018-11-30 rev.2 upload
2018-11-30 garv修正，謎のAirwire修正
2018-11-30 rev.2完成
2019-01-18 hoge

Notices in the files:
parts and their libraries:
SparkFun-IC-Comms: Licensing: Creative Commons ShareAlike 4.0 International - https://creativecommons.org/licenses/by-sa/4.0
